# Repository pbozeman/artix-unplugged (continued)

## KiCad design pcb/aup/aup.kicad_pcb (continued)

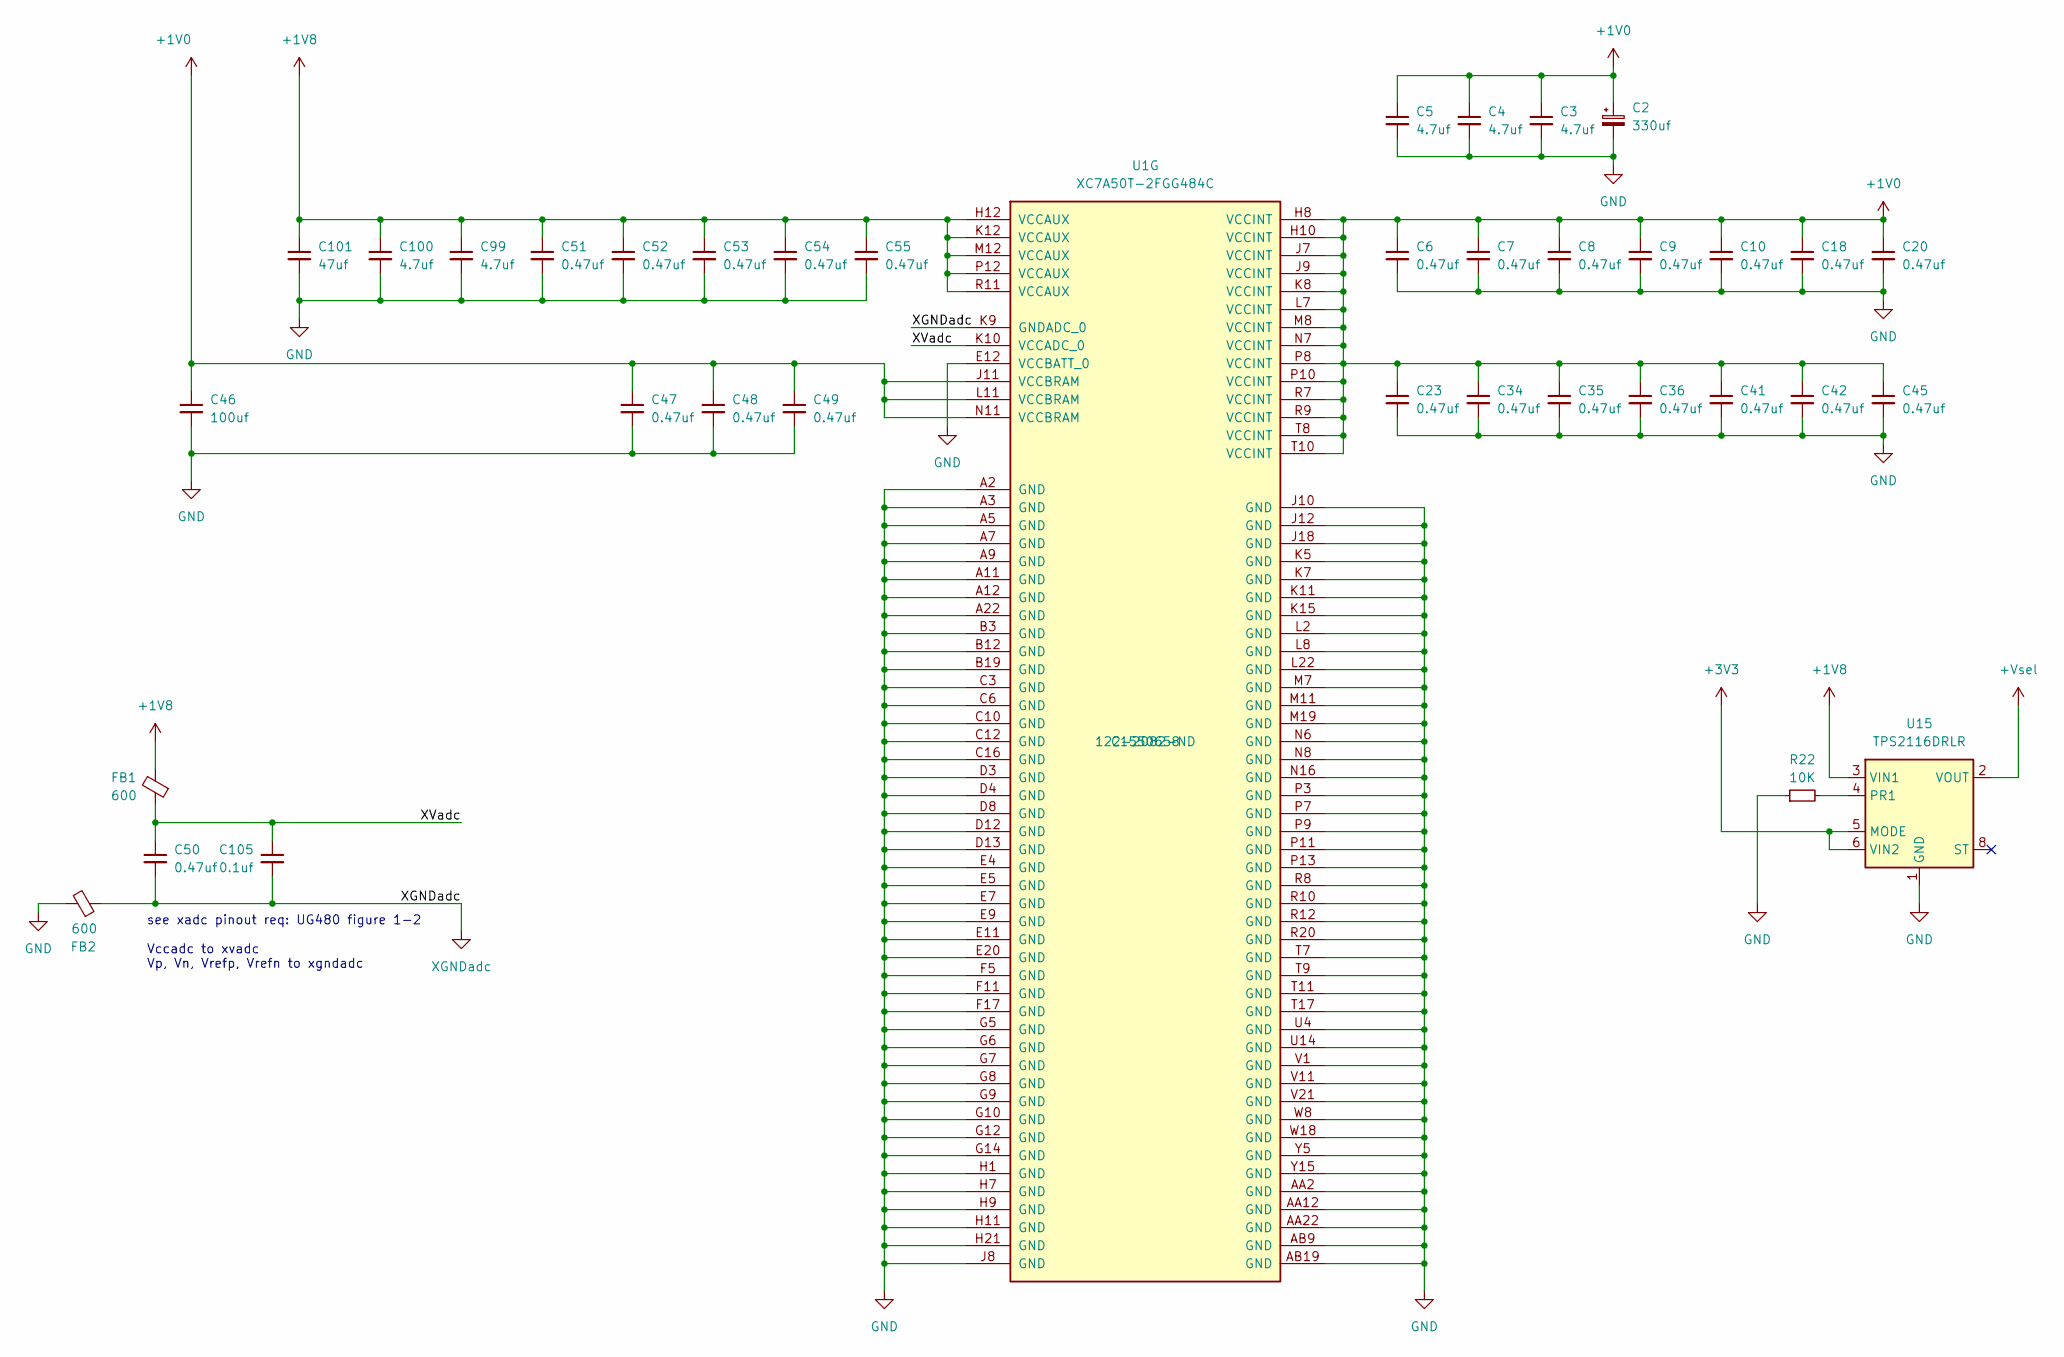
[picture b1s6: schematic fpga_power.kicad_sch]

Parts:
C2: 330uf; T520V; LCSC Part # C232383
C3, C4, C5, C99, C100: 4.7uf; C_0805_2012Metric; LCSC Part # C1779
C6, C7, C8, C9, C10, C18, C20, C23, C34, C35, C36, C41, C42, C45, C47, C48, C49, C50, C51, C52, C53, C54, C55: 0.47uf; C_0201_0603Metric; LCSC Part # C318543
C46: 100uf; C_1206_3216Metric; LCSC Part # C15008
C101: 47uf; C_1206_3216Metric; LCSC Part # C96123
C105: 0.1uf; C_0402_1005Metric; LCSC Part # C1525
FB1, FB2: 600; L_0402_1005Metric; LCSC Part # C76886
R22: 10K; R_0603_1608Metric; LCSC Part # C25804
U1: XC7A50T-2FGG484C; Xilinx_FGG484; LCSC Part # C1550658
U15: TPS2116DRLR; SOT-583-8; LCSC Part # C3235557

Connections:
+1V0: C2.1, C3.1, C4.1, C5.1, C6.1, C7.1, C8.1, C9.1, C10.1, C18.1, C20.1, C23.1, C34.1, C35.1, C36.1, C41.1, C42.1, C45.1, C46.1, C47.1, C48.1, C49.1, U1.H8 (VCCINT), U1.H10 (VCCINT), U1.J7 (VCCINT), U1.J9 (VCCINT), U1.J11 (VCCBRAM), U1.K8 (VCCINT), U1.L7 (VCCINT), U1.L11 (VCCBRAM), U1.M8 (VCCINT), U1.N7 (VCCINT), U1.N11 (VCCBRAM), U1.P8 (VCCINT), U1.P10 (VCCINT), U1.R7 (VCCINT), U1.R9 (VCCINT), U1.T8 (VCCINT), U1.T10 (VCCINT); also elsewhere on the board
+1V8: C51.1, C52.1, C53.1, C54.1, C55.1, C99.1, C100.1, C101.1, FB1.2, U1.H12 (VCCAUX), U1.K12 (VCCAUX), U1.M12 (VCCAUX), U1.P12 (VCCAUX), U1.R11 (VCCAUX), U15.3 (VIN1); also elsewhere on the board
+3V3: U15.5 (MODE), U15.6 (VIN2); also elsewhere on the board
+Vsel: U15.2 (VOUT), U15.7 (VOUT); also elsewhere on the board
/fpga_power/XVadc: C50.1, C105.1, FB1.1, U1.K10 (VCCADC_0)
GND: C2.2, C3.2, C4.2, C5.2, C6.2, C7.2, C8.2, C9.2, C10.2, C18.2, C20.2, C23.2, C34.2, C35.2, C36.2, C41.2, C42.2, C45.2, C46.2, C47.2, C48.2, C49.2, C51.2, C52.2, C53.2, C54.2, C55.2, C99.2, C100.2, C101.2, FB2.2, R22.1, U1.A2 (GND), U1.A3 (GND), U1.A5 (GND), U1.A7 (GND), U1.A9 (GND), U1.A11 (GND), U1.A12 (GND), U1.A22 (GND), U1.AA2 (GND), U1.AA12 (GND), U1.AA22 (GND), U1.AB9 (GND), U1.AB19 (GND), U1.B3 (GND), U1.B12 (GND), U1.B19 (GND), U1.C3 (GND), U1.C6 (GND), U1.C10 (GND), U1.C12 (GND), U1.C16 (GND), U1.D3 (GND), U1.D4 (GND), U1.D8 (GND), U1.D12 (GND), U1.D13 (GND), U1.E4 (GND), U1.E5 (GND), U1.E7 (GND), U1.E9 (GND), U1.E11 (GND), U1.E12 (VCCBATT_0), U1.E20 (GND), U1.F5 (GND), U1.F11 (GND), U1.F17 (GND), U1.G5 (GND), U1.G6 (GND), U1.G7 (GND), U1.G8 (GND), U1.G9 (GND), U1.G10 (GND), U1.G12 (GND), U1.G14 (GND), U1.H1 (GND), U1.H7 (GND), U1.H9 (GND), U1.H11 (GND), U1.H21 (GND), U1.J8 (GND), U1.J10 (GND), U1.J12 (GND), U1.J18 (GND), U1.K5 (GND), U1.K7 (GND), U1.K11 (GND), U1.K15 (GND), U1.L2 (GND), U1.L8 (GND), U1.L22 (GND), U1.M7 (GND), U1.M11 (GND), U1.M19 (GND), U1.N6 (GND), U1.N8 (GND), U1.N16 (GND), U1.P3 (GND), U1.P7 (GND), U1.P9 (GND), U1.P11 (GND), U1.P13 (GND), U1.R8 (GND), U1.R10 (GND), U1.R12 (GND), U1.R20 (GND), U1.T7 (GND), U1.T9 (GND), U1.T11 (GND), U1.T17 (GND), U1.U4 (GND), U1.U14 (GND), U1.V1 (GND), U1.V11 (GND), U1.V21 (GND), U1.W8 (GND), U1.W18 (GND), U1.Y5 (GND), U1.Y15 (GND), U15.1 (GND); also elsewhere on the board
unnamed: R22.2, U15.4 (PR1)
XGNDadc: C50.2, C105.2, FB2.1, U1.K9 (GNDADC_0); also elsewhere on the board

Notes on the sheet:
see xadc pinout req: UG480 figure 1-2 Vccadc to xvadc Vp, Vn, Vrefp, Vrefn to xgndadc

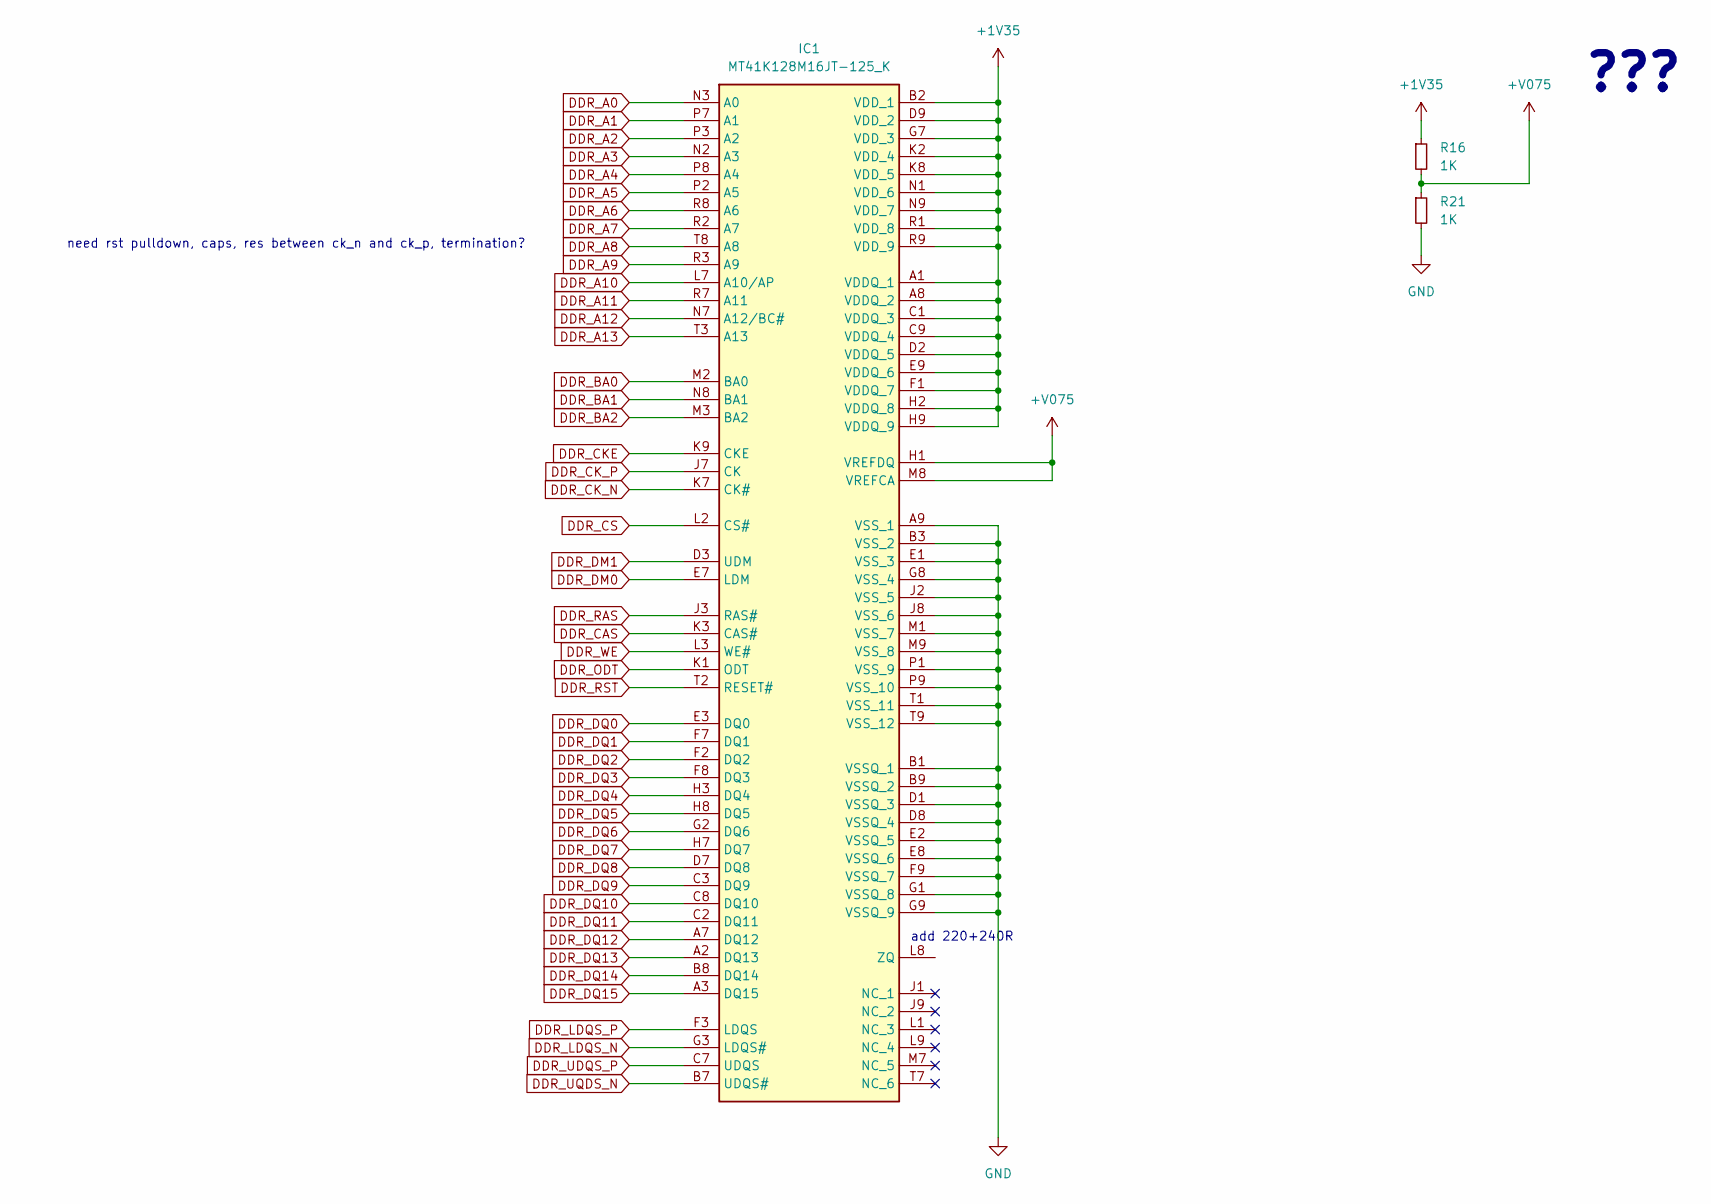
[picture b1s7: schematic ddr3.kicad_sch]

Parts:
IC1: MT41K128M16JT-125_K; BGA96C80P9X16_800X1400X120; LCSC Part # C36513
R16, R21: 1K; R_0603_1608Metric; LCSC Part # C4410

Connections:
+1V35: IC1.A1 (VDDQ_1), IC1.A8 (VDDQ_2), IC1.B2 (VDD_1), IC1.C1 (VDDQ_3), IC1.C9 (VDDQ_4), IC1.D2 (VDDQ_5), IC1.D9 (VDD_2), IC1.E9 (VDDQ_6), IC1.F1 (VDDQ_7), IC1.G7 (VDD_3), IC1.H2 (VDDQ_8), IC1.H9 (VDDQ_9), IC1.K2 (VDD_4), IC1.K8 (VDD_5), IC1.N1 (VDD_6), IC1.N9 (VDD_7), IC1.R1 (VDD_8), IC1.R9 (VDD_9), R16.1; also elsewhere on the board
+V075: IC1.H1 (VREFDQ), IC1.M8 (VREFCA), R16.2, R21.1
DDR_A0: IC1.N3 (A0); also elsewhere on the board
DDR_A1: IC1.P7 (A1); also elsewhere on the board
DDR_A2: IC1.P3 (A2); also elsewhere on the board
DDR_A3: IC1.N2 (A3); also elsewhere on the board
DDR_A4: IC1.P8 (A4); also elsewhere on the board
DDR_A5: IC1.P2 (A5); also elsewhere on the board
DDR_A6: IC1.R8 (A6); also elsewhere on the board
DDR_A7: IC1.R2 (A7); also elsewhere on the board
DDR_A8: IC1.T8 (A8); also elsewhere on the board
DDR_A9: IC1.R3 (A9); also elsewhere on the board
DDR_A10: IC1.L7 (A10/AP); also elsewhere on the board
DDR_A11: IC1.R7 (A11); also elsewhere on the board
DDR_A12: IC1.N7 (A12/BC#); also elsewhere on the board
DDR_A13: IC1.T3 (A13); also elsewhere on the board
DDR_BA0: IC1.M2 (BA0); also elsewhere on the board
DDR_BA1: IC1.N8 (BA1); also elsewhere on the board
DDR_BA2: IC1.M3 (BA2); also elsewhere on the board
DDR_CAS: IC1.K3 (CAS#); also elsewhere on the board
DDR_CKE: IC1.K9 (CKE); also elsewhere on the board
DDR_CK_N: IC1.K7 (CK#); also elsewhere on the board
DDR_CK_P: IC1.J7 (CK); also elsewhere on the board
DDR_CS: IC1.L2 (CS#); also elsewhere on the board
DDR_DM0: IC1.E7 (LDM); also elsewhere on the board
DDR_DM1: IC1.D3 (UDM); also elsewhere on the board
DDR_DQ0: IC1.E3 (DQ0); also elsewhere on the board
DDR_DQ1: IC1.F7 (DQ1); also elsewhere on the board
DDR_DQ2: IC1.F2 (DQ2); also elsewhere on the board
DDR_DQ3: IC1.F8 (DQ3); also elsewhere on the board
DDR_DQ4: IC1.H3 (DQ4); also elsewhere on the board
DDR_DQ5: IC1.H8 (DQ5); also elsewhere on the board
DDR_DQ6: IC1.G2 (DQ6); also elsewhere on the board
DDR_DQ7: IC1.H7 (DQ7); also elsewhere on the board
DDR_DQ8: IC1.D7 (DQ8); also elsewhere on the board
DDR_DQ9: IC1.C3 (DQ9); also elsewhere on the board
DDR_DQ10: IC1.C8 (DQ10); also elsewhere on the board
DDR_DQ11: IC1.C2 (DQ11); also elsewhere on the board
DDR_DQ12: IC1.A7 (DQ12); also elsewhere on the board
DDR_DQ13: IC1.A2 (DQ13); also elsewhere on the board
DDR_DQ14: IC1.B8 (DQ14); also elsewhere on the board
DDR_DQ15: IC1.A3 (DQ15); also elsewhere on the board
DDR_LDQS_N: IC1.G3 (LDQS#); also elsewhere on the board
DDR_LDQS_P: IC1.F3 (LDQS); also elsewhere on the board
DDR_ODT: IC1.K1 (ODT); also elsewhere on the board
DDR_RAS: IC1.J3 (RAS#); also elsewhere on the board
DDR_RST: IC1.T2 (RESET#); also elsewhere on the board
DDR_UDQS_P: IC1.C7 (UDQS); also elsewhere on the board
DDR_UQDS_N: IC1.B7 (UDQS#); also elsewhere on the board
DDR_WE: IC1.L3 (WE#); also elsewhere on the board
GND: IC1.A9 (VSS_1), IC1.B1 (VSSQ_1), IC1.B3 (VSS_2), IC1.B9 (VSSQ_2), IC1.D1 (VSSQ_3), IC1.D8 (VSSQ_4), IC1.E1 (VSS_3), IC1.E2 (VSSQ_5), IC1.E8 (VSSQ_6), IC1.F9 (VSSQ_7), IC1.G1 (VSSQ_8), IC1.G8 (VSS_4), IC1.G9 (VSSQ_9), IC1.J2 (VSS_5), IC1.J8 (VSS_6), IC1.M1 (VSS_7), IC1.M9 (VSS_8), IC1.P1 (VSS_9), IC1.P9 (VSS_10), IC1.T1 (VSS_11), IC1.T9 (VSS_12), R21.2; also elsewhere on the board

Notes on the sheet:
add 220+240R
???
need rst pulldown, caps, res between ck_n and ck_p, termination?

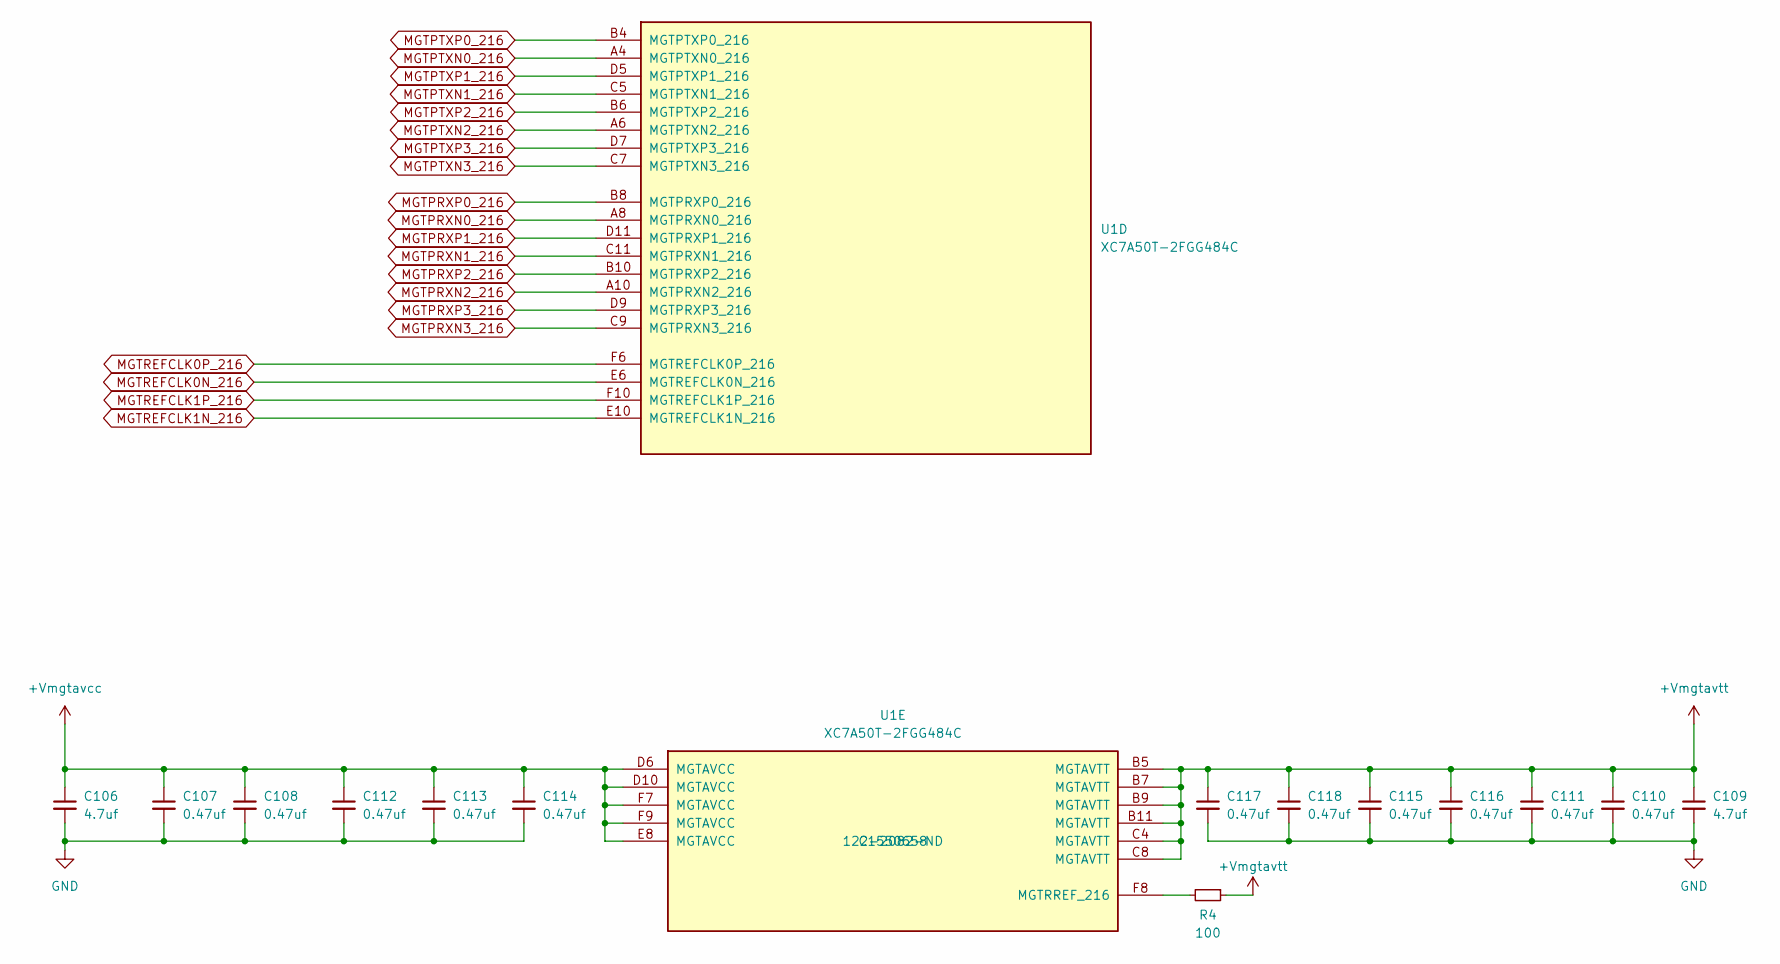
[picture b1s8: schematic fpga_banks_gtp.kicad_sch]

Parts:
C106, C109: 4.7uf; C_0805_2012Metric; LCSC Part # C1779
C107, C108, C110, C111, C112, C113, C114, C115, C116, C117, C118: 0.47uf; C_0201_0603Metric; LCSC Part # C318543
R4: 100; R_0201_0603Metric; LCSC Part # C270366
U1: XC7A50T-2FGG484C; Xilinx_FGG484; LCSC Part # C1550658

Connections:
+Vmgtavcc: C106.1, C107.1, C108.1, C112.1, C113.1, C114.1, U1.D6 (MGTAVCC), U1.D10 (MGTAVCC), U1.E8 (MGTAVCC), U1.F7 (MGTAVCC), U1.F9 (MGTAVCC); also elsewhere on the board
+Vmgtavtt: C109.1, C110.1, C111.1, C115.1, C116.1, C117.1, C118.1, R4.1, U1.B5 (MGTAVTT), U1.B7 (MGTAVTT), U1.B9 (MGTAVTT), U1.B11 (MGTAVTT), U1.C4 (MGTAVTT), U1.C8 (MGTAVTT); also elsewhere on the board
GND: C106.2, C107.2, C108.2, C109.2, C110.2, C111.2, C112.2, C113.2, C114.2, C115.2, C116.2, C117.2, C118.2; also elsewhere on the board
MGTPRXN0_216: U1.A8 (MGTPRXN0_216); also elsewhere on the board
MGTPRXN1_216: U1.C11 (MGTPRXN1_216); also elsewhere on the board
MGTPRXN2_216: U1.A10 (MGTPRXN2_216); also elsewhere on the board
MGTPRXN3_216: U1.C9 (MGTPRXN3_216); also elsewhere on the board
MGTPRXP0_216: U1.B8 (MGTPRXP0_216); also elsewhere on the board
MGTPRXP1_216: U1.D11 (MGTPRXP1_216); also elsewhere on the board
MGTPRXP2_216: U1.B10 (MGTPRXP2_216); also elsewhere on the board
MGTPRXP3_216: U1.D9 (MGTPRXP3_216); also elsewhere on the board
MGTPTXN0_216: U1.A4 (MGTPTXN0_216); also elsewhere on the board
MGTPTXN1_216: U1.C5 (MGTPTXN1_216); also elsewhere on the board
MGTPTXN2_216: U1.A6 (MGTPTXN2_216); also elsewhere on the board
MGTPTXN3_216: U1.C7 (MGTPTXN3_216); also elsewhere on the board
MGTPTXP0_216: U1.B4 (MGTPTXP0_216); also elsewhere on the board
MGTPTXP1_216: U1.D5 (MGTPTXP1_216); also elsewhere on the board
MGTPTXP2_216: U1.B6 (MGTPTXP2_216); also elsewhere on the board
MGTPTXP3_216: U1.D7 (MGTPTXP3_216); also elsewhere on the board
MGTREFCLK0N_216: U1.E6 (MGTREFCLK0N_216); also elsewhere on the board
MGTREFCLK0P_216: U1.F6 (MGTREFCLK0P_216); also elsewhere on the board
MGTREFCLK1N_216: U1.E10 (MGTREFCLK1N_216); also elsewhere on the board
MGTREFCLK1P_216: U1.F10 (MGTREFCLK1P_216); also elsewhere on the board
unnamed: R4.2, U1.F8 (MGTRREF_216)

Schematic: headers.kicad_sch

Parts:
J1, J2: QSH-060-01-L-D-A; SAMTEC_QSH-060-01-X-D-A
J3, J4: QTH-060-01-L-D-A; SAMTEC_QTH-060-01-X-D-A
J5: QSH-030-01-L-D-A; SAMTEC_QSH-030-01-X-D-A
J6: QTH-030-01-L-D-A; SAMTEC_QTH-030-01-X-D-A

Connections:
+3V3: J1.9, J1.10, J1.19, J1.20, J1.29, J1.30, J1.39, J1.40, J1.49, J1.50, J1.71, J1.72, J1.81, J1.82, J1.91, J1.92, J1.101, J1.102, J1.111, J1.112, J2.9, J2.10, J2.19, J2.20, J2.29, J2.30, J2.39, J2.40, J2.49, J2.50, J2.71, J2.72, J2.81, J2.82, J2.91, J2.92, J2.101, J2.102, J2.111, J2.112, J3.9, J3.10, J3.19, J3.20, J3.29, J3.30, J3.39, J3.40, J3.49, J3.50, J3.71, J3.72, J3.81, J3.82, J3.91, J3.92, J3.101, J3.102, J3.111, J3.112, J4.9, J4.10, J4.19, J4.20, J4.29, J4.30, J4.39, J4.40, J4.49, J4.50, J4.71, J4.72, J4.81, J4.82, J4.91, J4.92, J4.101, J4.102, J4.111, J4.112; also elsewhere on the board
GND: J1.GND, J2.GND, J3.GND, J4.GND; also elsewhere on the board
IOB_52: J2.104, J4.104
IOB_53: J2.105, J4.105
IOB_54: J2.116, J4.116
IOB_55: J2.99, J4.99
IOB_56: J2.108, J4.108
IOB_57: J2.119, J4.119
IOB_58: J2.118, J4.118
IOB_59: J2.89, J4.89
IOB_60: J2.73, J4.73
IOB_61: J2.117, J4.117
IOB_63: J2.115, J4.115
IOB_64: J2.114, J4.114
IOB_66: J2.96, J4.96
IOB_67: J2.100, J4.100
IOB_68: J2.98, J4.98
IOB_69: J2.113, J4.113
IOB_71: J2.109, J4.109
IOB_72: J2.88, J4.88
IOB_73: J2.107, J4.107
IOB_74: J2.84, J4.84
IOB_75: J2.103, J4.103
IOB_76: J2.97, J4.97
IOB_77: J2.110, J4.110
IOB_78: J2.86, J4.86
IOB_79: J2.93, J4.93
IOB_80: J2.90, J4.90
IOB_81: J2.87, J4.87
IOB_82: J2.106, J4.106
IOB_83: J2.95, J4.95
IOB_84: J2.83, J4.83
IOB_85: J2.80, J4.80
IOB_86: J2.76, J4.76
IOB_87: J2.74, J4.74
IOB_88: J2.85, J4.85
IOB_89: J2.79, J4.79
IOB_91: J2.65, J4.65
IOB_92: J2.67, J4.67
IOB_93: J2.66, J4.66
IOB_94: J2.75, J4.75
IOB_98: J2.64, J4.64
IOB_99: J2.78, J4.78
IOB_100: J2.63, J4.63
IOB_101: J2.62, J4.62
IOB_102: J2.61, J4.61
IOB_103_CBSEL0: J2.94, J4.94
IOB_103_CBSEL1: J2.69, J4.69
IOB_105_SDO: J2.68, J4.68
IOB_106_SDI: J2.70, J4.70
IOB_107_SCK: J2.77, J4.77
IOL_1A: J1.63, J3.63
IOL_1B: J1.62, J3.62
IOL_2A: J1.61, J3.61
IOL_2B: J1.64, J3.64
IOL_3A: J1.68, J3.68
IOL_3B: J1.66, J3.66
IOL_4A: J1.79, J3.79
IOL_4B: J1.70, J3.70
IOL_5A: J1.65, J3.65
IOL_5B: J1.74, J3.74
IOL_6A: J1.87, J3.87
IOL_6B: J1.67, J3.67
IOL_7A: J1.103, J3.103
IOL_7B: J1.90, J3.90
IOL_8A: J1.83, J3.83
IOL_8B: J1.75, J3.75
IOL_9A: J1.95, J3.95
IOL_9B: J1.78, J3.78
IOL_10A: J1.69, J3.69
IOL_10B: J1.76, J3.76
IOL_11A: J1.99, J3.99
IOL_11B: J1.84, J3.84
IOL_12A: J1.107, J3.107
IOL_12B: J1.88, J3.88
IOL_13A: J1.77, J3.77
IOL_13B: J1.80, J3.80
IOL_14B: J1.86, J3.86
IOL_15A: J1.96, J3.96
IOL_15B: J1.94, J3.94
IOL_16A: J1.98, J3.98
IOL_16B: J1.115, J3.115
IOL_17A: J1.97, J3.97
IOL_17B: J1.100, J3.100
IOL_18A: J1.89, J3.89
IOL_18B: J1.106, J3.106
IOL_19A: J1.73, J3.73
IOL_19B: J1.119, J3.119
IOL_20A: J1.85, J3.85
IOL_20B: J1.104, J3.104
IOL_21A: J1.105, J3.105
IOL_21B: J1.108, J3.108
IOL_22A: J1.117, J3.117
IOL_22B: J1.118, J3.118
IOL_23A: J1.93, J3.93
IOL_23B: J2.120, J4.120
IOL_24A: J1.110, J3.110
IOL_24B: J1.120, J3.120
IOL_25A: J1.114, J3.114
IOL_25B: J1.113, J3.113
IOL_26A: J1.116, J3.116
IOL_26B: J1.109, J3.109
IOR_109: J2.47, J4.47
IOR_110: J2.59, J4.59
IOR_111: J2.58, J4.58
IOR_112: J2.55, J4.55
IOR_113: J2.57, J4.57
IOR_114: J2.46, J4.46
IOR_115: J2.54, J4.54
IOR_116: J2.42, J4.42
IOR_117: J2.53, J4.53
IOR_118: J2.60, J4.60
IOR_119: J2.43, J4.43
IOR_120: J2.52, J4.52
IOR_121: J2.45, J4.45
IOR_122: J2.36, J4.36
IOR_123: J2.51, J4.51
IOR_126: J2.38, J4.38
IOR_127: J2.41, J4.41
IOR_128: J2.56, J4.56
IOR_129: J2.37, J4.37
IOR_130: J2.25, J4.25
IOR_131: J2.33, J4.33
IOR_133: J2.35, J4.35
IOR_134: J2.48, J4.48
IOR_136: J2.34, J4.34
IOR_137: J2.44, J4.44
IOR_138: J2.27, J4.27
IOR_139: J2.32, J4.32
IOR_140: J2.26, J4.26
IOR_141: J2.31, J4.31
IOR_142: J2.28, J4.28
IOR_143: J2.23, J4.23
IOR_144: J2.22, J4.22
IOR_145: J2.21, J4.21
IOR_146: J2.18, J4.18
IOR_147: J2.15, J4.15
IOR_148: J2.2, J4.2
IOR_149: J2.17, J4.17
IOR_150: J2.14, J4.14
IOR_151: J2.13, J4.13
IOR_152: J2.24, J4.24
IOR_153: J2.7, J4.7
IOR_154: J2.6, J4.6
IOR_155: J2.16, J4.16
IOR_156: J2.4, J4.4
IOR_157: J2.11, J4.11
IOR_160: J2.12, J4.12
IOR_161: J2.3, J4.3
IOR_162: J2.8, J4.8
IOR_165: J2.1, J4.1
IOR_167: J2.5, J4.5
IOT_168: J1.22, J3.22
IOT_169: J1.16, J3.16
IOT_171: J1.4, J3.4
IOT_172: J1.8, J3.8
IOT_173: J1.7, J3.7
IOT_176: J1.2, J3.2
IOT_177: J1.32, J3.32
IOT_178: J1.6, J3.6
IOT_179: J1.15, J3.15
IOT_180: J1.1, J3.1
IOT_181: J1.11, J3.11
IOT_182: J1.12, J3.12
IOT_183: J1.26, J3.26
IOT_184: J1.18, J3.18
IOT_185: J1.13, J3.13
IOT_186: J1.24, J3.24
IOT_187: J1.14, J3.14
IOT_190: J1.5, J3.5
IOT_191: J1.21, J3.21
IOT_192: J1.23, J3.23
IOT_193: J1.17, J3.17
IOT_194: J1.28, J3.28
IOT_196: J1.3, J3.3
IOT_197: J1.31, J3.31
IOT_198: J1.47, J3.47
IOT_199: J1.34, J3.34
IOT_200: J1.27, J3.27
IOT_203: J1.36, J3.36
IOT_205: J1.38, J3.38
IOT_206: J1.43, J3.43
IOT_207: J1.42, J3.42
IOT_208: J1.46, J3.46
IOT_209: J1.25, J3.25
IOT_210: J1.35, J3.35
IOT_211: J1.44, J3.44
IOT_212: J1.51, J3.51
IOT_213: J1.52, J3.52
IOT_214: J1.54, J3.54
IOT_215: J1.55, J3.55
IOT_216: J1.48, J3.48
IOT_218: J1.58, J3.58
IOT_219: J1.33, J3.33
IOT_220: J1.60, J3.60
IOT_221: J1.37, J3.37
IOT_222: J1.41, J3.41
IOT_223: J1.56, J3.56
IOT_224: J1.53, J3.53
IOT_225: J1.59, J3.59
IOT_226: J1.57, J3.57
IOT_227: J1.45, J3.45
MGTPRXN0_216: J5.40; also elsewhere on the board
MGTPRXN1_216: J5.28; also elsewhere on the board
MGTPRXN2_216: J5.32; also elsewhere on the board
MGTPRXN3_216: J5.36; also elsewhere on the board
MGTPRXP0_216: J5.38; also elsewhere on the board
MGTPRXP1_216: J5.26; also elsewhere on the board
MGTPRXP2_216: J5.30; also elsewhere on the board
MGTPRXP3_216: J5.34; also elsewhere on the board
MGTPTXN0_216: J5.58, J6.58; also elsewhere on the board
MGTPTXN1_216: J5.54; also elsewhere on the board
MGTPTXN2_216: J5.50; also elsewhere on the board
MGTPTXN3_216: J5.46; also elsewhere on the board
MGTPTXP0_216: J5.60, J6.60; also elsewhere on the board
MGTPTXP1_216: J5.56; also elsewhere on the board
MGTPTXP2_216: J5.52; also elsewhere on the board
MGTPTXP3_216: J5.48; also elsewhere on the board
MGTREFCLK0N_216: J5.44; also elsewhere on the board
MGTREFCLK0P_216: J5.42; also elsewhere on the board
MGTREFCLK1N_216: J5.24; also elsewhere on the board
MGTREFCLK1P_216: J5.22; also elsewhere on the board

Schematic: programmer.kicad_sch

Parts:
C43, C44: 30pf; C_0603_1608Metric; LCSC Part # C1658
U11: FT2232HQ; LCSC Part # C193662
U12: 93LC56BT-I/OT; SOT-23-6; LCSC Part # C190271
U13: MX25L3233FM2; SOIC-8_5.3x5.3mm_P1.27mm; LCSC Part # C190802
Y1: 12MHz/20pf; Crystal_SMD_3225-4Pin_3.2x2.5mm; LCSC Part # C9002

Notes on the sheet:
this doesn't match footprint

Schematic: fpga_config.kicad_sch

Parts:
C102, C103: 0.47uf; C_0201_0603Metric; LCSC Part # C318543
C104: 47uf; C_1206_3216Metric; LCSC Part # C96123
U1: XC7A50T-2FGG484C; Xilinx_FGG484; LCSC Part # C1550658

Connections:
+3V3: C102.1, C103.1, C104.1, U1.F12 (VCCO_0), U1.T12 (VCCO_0); also elsewhere on the board
GND: C102.2, C103.2, C104.2, U1.N9 (DXN_0), U1.N10 (DXP_0); also elsewhere on the board
XGNDadc: U1.L9 (VREFN_0), U1.L10 (VP_0), U1.M9 (VN_0), U1.M10 (VREFP_0); also elsewhere on the board

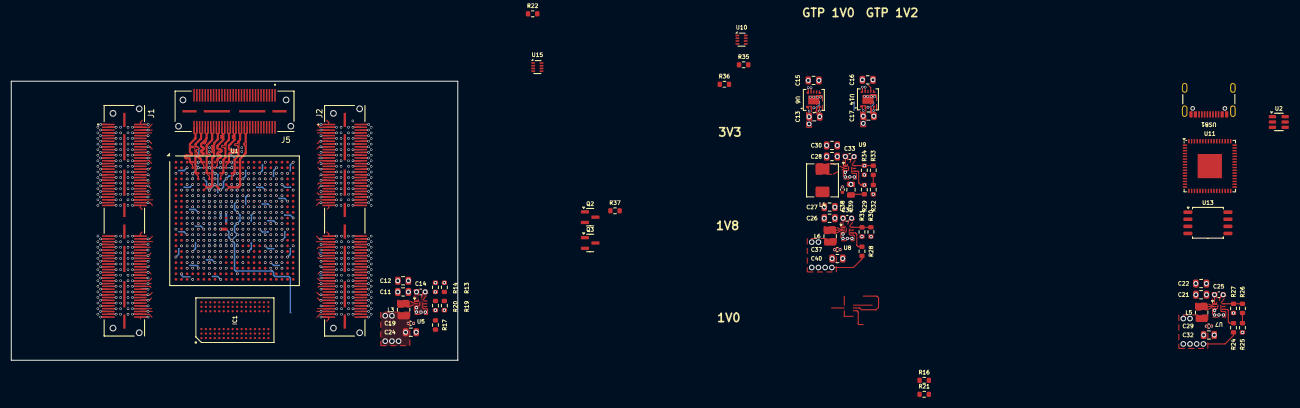
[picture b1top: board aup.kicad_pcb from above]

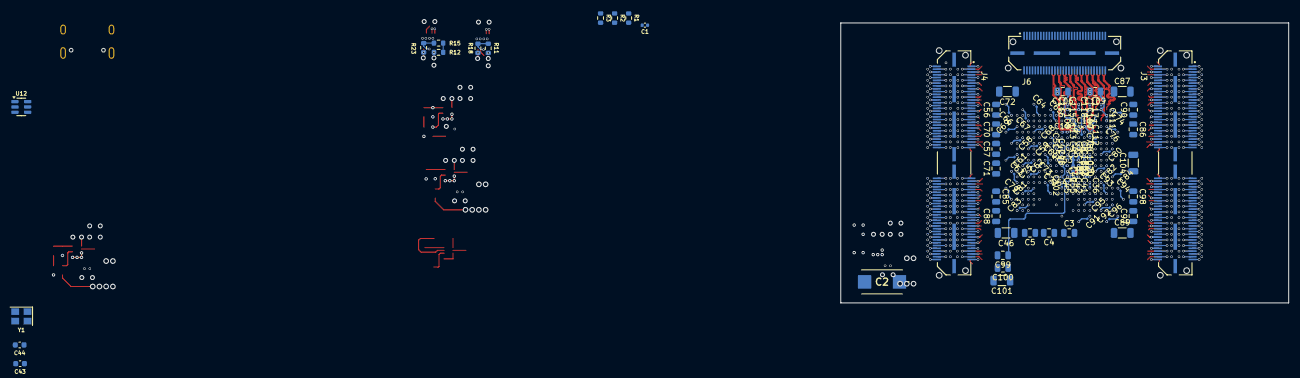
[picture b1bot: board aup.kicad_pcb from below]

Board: 8 copper layers, 80.0 x 50.0 mm, 179 parts (110 on the bottom side), 313 nets.

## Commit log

2025-04-15 add kicad-base
2025-04-15 Add power design doc
2025-04-16 Add .gitignore
2025-04-16 External power with usb and barrel jack
2025-04-16 Add 5v regulator to external power portion
2025-04-17 Start of fpga voltage rails. Added 1v0/vccint
2025-04-17 Fix footnote for Vccbram in docs
2025-04-18 Finished voltage rail schematic
2025-04-18 Added symbols for the major components
    It should be possible to do a first pass placement of ICs on the pcb as
    a rough fit check.
    Most imported footprints are still missing models.
2025-04-18 Initial layout for Vccint
2025-04-18 Rough high level layout plan
2025-04-18 ADC vref notes
2025-04-18 Redo high level layout for, hopefully, better power routing
2025-04-19 Update voltage rail decisions
2025-04-19 First pass on upper voltage rails
2025-04-19 Minor drc fixes
2025-04-19 First pass on lower rails
2025-04-19 Fix L1 footprint and add reg and ftdi models
2025-04-19 Update footprints and 3d models. All render
2025-04-19 Relative path fixes
2025-04-20 Improve FB nets for lower EMI. Route 5V out to regs
2025-04-23 Update rail switch decision
2025-04-23 Add some todo's on schematic. Add vias to fpga
2025-04-23 Add power doc notes for GTA
2025-04-23 Add netnames for rails
2025-04-23 Use TPS2116DRLR for Vin mux
2025-04-23 Redid bga vias
2025-04-23 Start to add net class color
2025-04-23 Start of regulator rework
2025-04-23 GTP 1.0 and 1.2 LDOs routed
2025-04-24 Recovered 1v35
2025-04-25 Cleanup power layout
2025-04-25 Very rough assigment for DDR to banks
2025-04-26 All rails assigned net classes
2025-04-26 IO bank netclass assignments
2025-04-27 Align fpga in daughter area
2025-04-27 Switch to 50 pin sockets
2025-04-28 Various explorations of layout
    The pcb file is a mess with options. Saving this in a branch
    to revisit it after interim layout.
2025-05-06 Switch to QSH-60
2025-06-04 Misc updates - too hard to see in a diff after a delay
2025-06-04 Planning upsized layout
2025-06-05 More upsized planning
2025-06-05 Add upper connector
2025-06-07 Add capacitor requirements
2025-06-07 Add cap decision overrides
2025-06-07 Add hierarchical sheets for banks and add caps.
    There are some stale sheets in this commit, but I don't want to delete
    an active one accidentally. Save them all for now, and then go back and
    clean them up.
2025-06-07 Added more passives
2025-06-08 Switch 0.47uf caps under bga to 0201
2025-06-08 Add GTP passives
2025-06-09 Start working out GTP diff pair routing
2025-06-09 GTP diff pairs routed, but not tuned
2025-06-09 Mid GTP tuning
2025-06-09 GTP left side tuned
2025-06-10 Initial GTP tuning
